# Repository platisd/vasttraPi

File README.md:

# VasttraPi
Your personal departures screen for Västtrafik buses. Currently it is hardcoded to look for buses going from Lindholmen to the center, but can be easily modified or extended. It uses a Python wrapper ([PyTrafik](https://github.com/axelniklasson/PyTrafik)), around the Västtrafik API by Axel Niklasson. Read more about the project and its background [here](https://platis.solutions/blog/2017/06/18/vasttrapi-my-personalized-vasttrafik-bus-stop/).

## How to install
First, prepare your Raspberry Pi for connecting with your local wireless network and enable SSH. The following guide has been tested on **2017-03-02-raspbian-jessie** running on a **Raspberry Pi Zero W**.

* Set the correct timezone to your Pi
  * `sudo raspi-config`
  * Localisation Options
  * Change timezone
  * Europe
  * Stockholm
* Clone the vasttraPi repository
  * `git clone https://github.com/platisd/vasttraPi.git`
* Clone the PyTrafik repository
  * `git clone https://github.com/axelniklasson/PyTrafik.git`
* Install the PyTrafik Python3 module
  * `sudo pip3 install PyTrafik/`
* Make sure you have PySerial 3.3 or greater installed
  * sudo pip3 install pyserial --upgrade
* Create an api-config file with your [Västtrafik API tokens](https://developer.vasttrafik.se/portal/#/applications)
  * `nano vasttraPi/api-config`
  * Add your API tokens. The first line should be the (public) key and the second is the secret.

* Make the Python3 GUI start right after boot
  * `nano /home/pi/.xsession`
  * Add: `python3 /home/pi/vasttraPi/departures.py`
  * To undo this, do not just empty the .xsession file, remove it completely.
* Sync, reboot and the departures screen should pop up
  * `sync`
  * `sudo reboot`

### Read-only & OverlayFS (Optional)
The Python3 script, which is configured to run on startup, is listening to the serial port for an "off" string in order to shutdown the Raspberry Pi. This is done in order to protect the SD card from being corrupted, even though this has rarely happened to me. That being said, if you do not want to bother with the extra USB-serial connection or feel like trying something new, an effective way of protecting the SD card is by using a read-only filesystem and OverlayFS. After a lot of search I found the great [instructions](http://wiki.psuter.ch/doku.php?id=solve_raspbian_sd_card_corruption_issues_with_read-only_mounted_root_partition) by Pascal Suter who provided a very useful [script](overlayRoot.sh) in order to achieve that.

* Copy the `overlayRoot.sh` script to `/sbin/`
  * `sudo cp /home/pi/vasttraPi/overlayRoot.sh /sbin/`
* Disable swap
  * `sudo dphys-swapfile swapoff`
  * `sudo dphys-swapfile uninstall`
  * `sudo update-rc.d dphys-swapfile remove`
* Once you have your partitions set up the way you want them edit the `/boot/cmdline.txt` to run the `overlayRoot.sh` script.
  * `nano /boot/cmdline.txt`
  * Append `init=/sbin/overlayRoot.sh` to the end of the existing file.
* After rebooting, any changes to the partitions will be non-persistent. If you want to undo this, simply restore the `/boot/cmdline.txt` to its original state.

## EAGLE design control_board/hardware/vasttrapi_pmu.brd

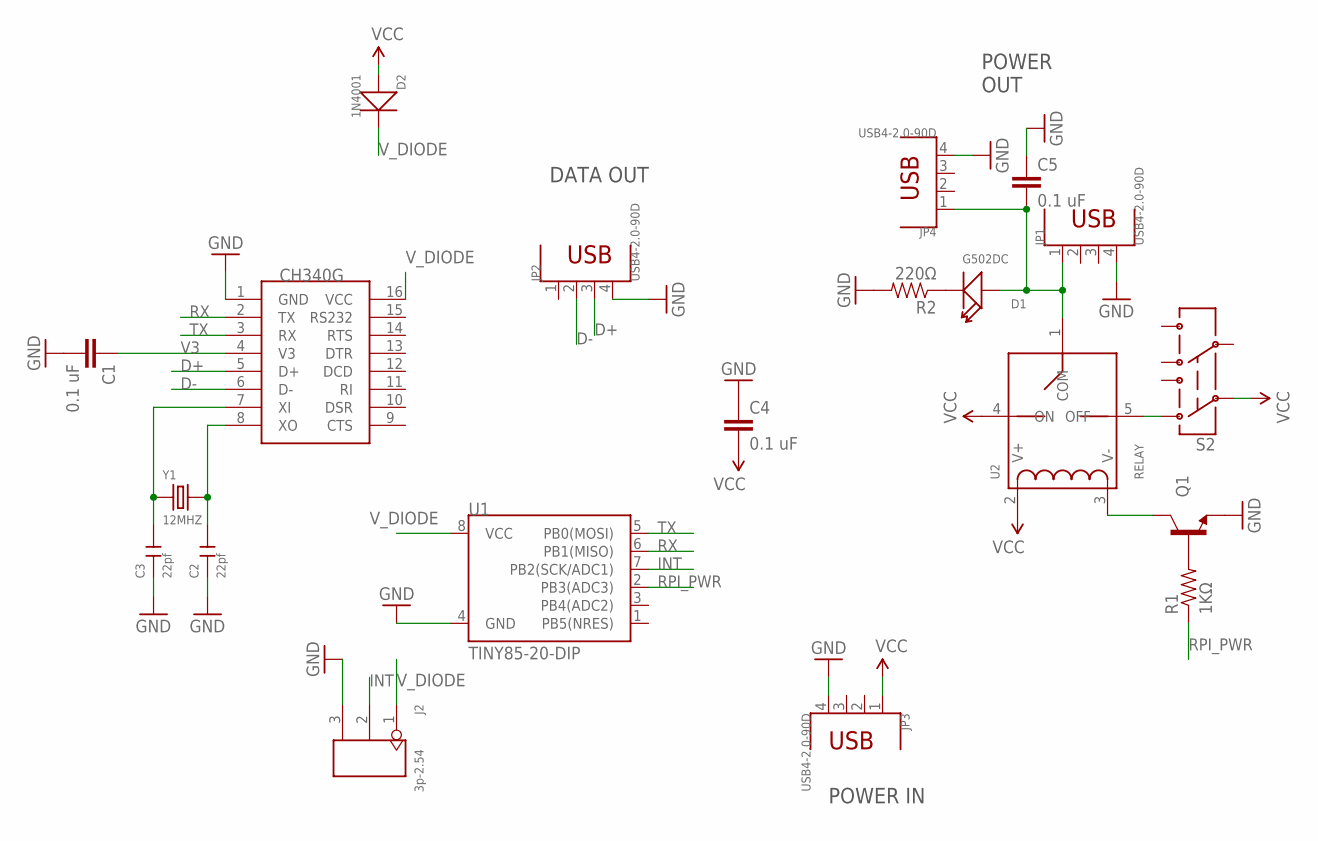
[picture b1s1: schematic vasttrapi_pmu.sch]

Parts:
C1, C4, C5: 0.1 uF; CAP-PTH-SMALL-KIT
C2, C3: 22pf; CERAMIC-2.54
D1: G502DC; LED2-2.54-D5.0MM
D2: 1N4001; DO-41
J2: 3p-2.54; H3-2.54
JP1, JP2, JP3, JP4: USB4-2.0-90D; USB4+2P-2.0-90D
Q1: TRANSISTOR_NPNBC547; TO-92-AMMO
R1: 1KΩ; AXIAL-0.4
R2: 220Ω; AXIAL-0.4
S2: SWITCH-DPDTOS; OS
U1: TINY85-20-DIP; DIP08
U2: RELAY
U$1: CH340G; SOIC16
Y1: 12MHZ; HC49US

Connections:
D+: JP2.3 (2), U$1.5 (D+)
D-: JP2.2 (3), U$1.6 (D-)
GND: C1.2, C2.1, C3.1, C4.1, C5.1, J2.3, JP1.4 (1), JP2.4 (1), JP3.4 (1), JP4.4 (1), Q1.3 (E), R2.P$2 (2), U1.4 (GND), U$1.1 (GND)
INT: J2.2, U1.7 (PB2(SCK/ADC1))
unnamed: Q1.2 (B), R1.P$2 (2)
unnamed: Q1.1 (C), U2.3 (V-)
unnamed: S2.1, U2.5 (OFF)
unnamed: C2.2, U$1.8 (XO), Y1.2
unnamed: C3.2, U$1.7 (XI), Y1.1
unnamed: D1.-, R2.P$1 (1)
RPI_PWR: R1.P$1 (1), U1.2 (PB3(ADC3))
RX: U1.6 (PB1(MISO)), U$1.2 (TX)
TX: U1.5 (PB0(MOSI)), U$1.3 (RX)
V3: C1.1, U$1.4 (V3)
VCC: C4.2, D2.1 (+), JP3.1 (5), S2.2, U2.2 (V+), U2.4 (ON)
VRPI: C5.2, D1.+, JP1.1 (5), JP4.1 (5), U2.1 (COM)
V_DIODE: D2.2 (-), J2.1, U1.8 (VCC), U$1.16 (VCC)

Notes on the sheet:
POWER IN
POWER OUT
DATA OUT

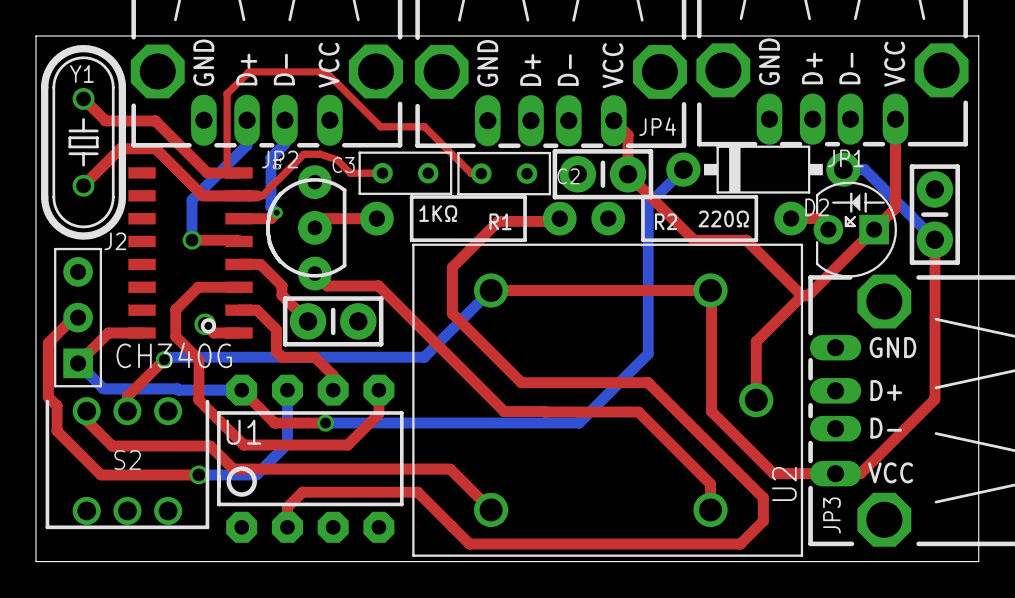
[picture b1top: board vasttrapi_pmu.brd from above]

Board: 2 copper layers, 52.4 x 29.2 mm, 21 parts (0 on the bottom side), 17 nets.

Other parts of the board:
U$3: OSHWLOGO_BACK_0.2

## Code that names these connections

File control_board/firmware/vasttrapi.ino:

/**
   Power Control board for the Raspberry Pi using an ATTinyx5 microcontroller.
   The Power Control board is using a relay to turn on and off the power to a Raspberry Pi.
   Additionally, they are connected via (software) UART for communication when the RPi is on.
   The microcontroller connected to a capacitive touch sensor which allows interaction with
   the external user that wants to turn the Raspberry Pi on and off.

   ==== STATES ====
   The microcontroller has the following states:
   - Sleep state where the microcontroller is in deep sleep and the power to the RPi is OFF.
   - Operation state where the microcontroller is triggering the relay to power on the RPi and
   can communication to it via UART.
   - Shutdown state where the microcontroller sends a UART instruction to the RPi to begin its
   shutdown sequence, in order to avoid damaging the SD card by abruptly turning the power off.

   ==== CURRENT FUNCTIONALITY ====
   Upon starting up, the microcontroller goes in deep sleep which can be interrupted by a HIGH
   signal coming from the capacitive sensor. This initiates a window of operation for the Raspberry Pi
   during which it will remain on. Every consecutive touch moves the end of this window further in the
   future, therefore, prolonging the period that the Raspberry Pi is functioning. In other words, on
   every touch, the operation gets extended for the specified amount of time.
*/

#include <avr/sleep.h>    // Sleep Modes
#include <avr/power.h>    // Power management

const unsigned short touchSensorPin = PB2;
const unsigned short rpiPwrPin = PB3;
const boolean powerOnState = HIGH; // The rpiPwrPin state that turns the power on to the RPi

volatile unsigned long timeToSleep = 0;
const unsigned long awakePeriod = 600000UL; // Time in milliseconds to remain awake on every new touch
const unsigned long shutdownTime = 12000; // Time in milliseconds to wait for the RPi to shutdown

enum PowerState {
  SLEEP,
  OPERATION,
  SHUTDOWN
};
PowerState currentState = SLEEP; // Begin in a deep sleep state

/**
   The change interrupt callback
*/
ISR (PCINT0_vect) {
  // We register a touch event only when the signal from the touchSensor is rising
  // Ignore touch events while in shutdown state
  if (currentState != SHUTDOWN && digitalRead(touchSensorPin) == HIGH) {
    timeToSleep = millis() + awakePeriod;
  }
}

/**
   Makes the microcontroller go to deep sleep until a change interrupt occurs
*/
void goToSleep() {
  set_sleep_mode(SLEEP_MODE_PWR_DOWN);
  ADCSRA = 0; // turn off ADC
  power_all_disable (); // power off ADC, Timer 0 and 1, serial interface
  sleep_enable();
  sleep_cpu(); // Sleep here and wait for the interrupt
  sleep_disable();
  power_all_enable(); // power everything back on
}

void turnRPiPowerOn() {
  digitalWrite(rpiPwrPin, powerOnState);
}

void turnRPiPowerOff() {
  digitalWrite(rpiPwrPin, !powerOnState);
}

/**
   UART command sent to the RPi to trigger its shutdown sequence
*/
void signalShutdown() {
  Serial.println("off");
  Serial.flush(); // Make sure that UART output has been transmitted before exiting this method
}

/**
   Wait for the RPi to shutdown properly. In the future more logic might be added here.
*/
void waitForRPiShutdown() {
  delay(shutdownTime);
}

void setup() {
  Serial.begin(9600); // The Universal ATtinyCore library by Spence Konde uses PB0 as TX and PB1 as RX
  pinMode(rpiPwrPin, OUTPUT);
  pinMode(touchSensorPin, INPUT);
  // Setup pin change interrupt for D2
  PCMSK |= bit (PCINT2); // want pin D2 (PB2)
  GIFR |= bit (PCIF); // clear any outstanding interrupts
  GIMSK |= bit (PCIE); // enable pin change interrupts
}

void loop() {
  switch (currentState) {
    case SLEEP:
      turnRPiPowerOff(); // Cut off the power to the RPi
      goToSleep(); // Deep sleep until a change interrupt at the specified pin is triggered
      currentState = OPERATION; // If we reach this, it means that a touch was registered so we should be operating
      break;
    case OPERATION:
      turnRPiPowerOn(); // Turn on the power to the RPi (if this is already on, it won't make any difference)
      if (millis() >= timeToSleep) { // Check if it is currently time to be asleep
        // If we were operational but it's time to sleep, then we should move to the shutdown state
        currentState = SHUTDOWN;
      }
      break;
    case SHUTDOWN:
      signalShutdown(); // Send a command via UART to the RPi which will make it initiate a shutdown sequence
      waitForRPiShutdown(); // Wait for the RPi to shutdown, while disabling interrupts so new touch events are not logged
      // Now that we should be certain that the RPi has shut down, we can put our state to SLEEP
      currentState = SLEEP;
      break;
    default:
      break;
  }
}

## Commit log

2017-04-09 Added NTP time and the Teknikgatan station
2017-04-09 Disable screen blanking on the pi
2017-04-09 Changing the current directory so it can be called from different folders
2017-04-09 Actual departures shown
    TO-DO: Align destinations, map bus number to destination
2017-04-09 Work in progress, added top frames and next trips as a list of tuples
2017-04-09 Smaller font size for destination when on the Pi
    Also GUI is full screen when running on the pi
2017-04-09 Do not display departures that are too far away in the future
2017-04-09 Destinations column aligned and departures sorted
2017-04-09 Row frames initial implementation
2017-04-09 Added some documentation, removed unused imports
2017-04-09 Time left calculated for the next two trips of every bus
2017-04-09 Remove the previous departures before drawing the new ones
2017-04-09 pep8 formatting fixes
    Ran with: pep8 --ignore=E501 departures.py
2017-04-09 Only refresh the display when there is a change in departures
2017-04-09 Updated readme with installation instructions
2017-04-09 Initializing the connection only once
2017-04-09 Using system time if NTP server is not responding
2017-04-09 Re-initializing auth every hour
2017-04-10 Update README
    Instructions on how to undo the automatic gui startup
2017-04-22 Rev.1 power control board schematics
2017-04-22 Firmware for the control board MCU
2017-04-23 Adding serial command towards RPi to signal its shutdown process
    Aesthetic changes in comments etc
2017-04-23 Using explicit states instead
2017-04-23 Shutting down the Pi upon receiving UART instruction
2017-04-23 Updated pyserial installation instructions
2017-04-24 Polling serial in a separate thread
    In order to decouple it from the gui update and increase the polling rate
2017-05-18 Code changes as per hw rev.1 and later
2017-05-18 hw rev.2
    Added diode before the MCU, serial-to-usb chip and sensor
2017-05-18 small fix to switch footprint
2017-05-18 led position fix
2017-06-17 Explicitly declaring large number as unsigned longs
2017-06-17 Add OverlayFS script and instructions how to use it
    Also general polishing to the README
2017-06-19 Add the new bus line 58 to Bergsjon
2017-06-19 Ignore pycache
2017-06-29 Add link to article and photo
2017-07-08 Get destination name dynamically from the API
    The destinations were previously hardcoded depending on the
    bus line number which is not so sustainable and not always
    accurate, since the destination for each bus line can vary.
2017-07-08 Change color to yellow for better visibility
    Especially at steep angles the text on the gray lines was not visible

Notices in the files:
parts and their libraries:
SparkFun-DigitalIC: Licensing: Creative Commons ShareAlike 4.0 International - https://creativecommons.org/licenses/by-sa/4.0
